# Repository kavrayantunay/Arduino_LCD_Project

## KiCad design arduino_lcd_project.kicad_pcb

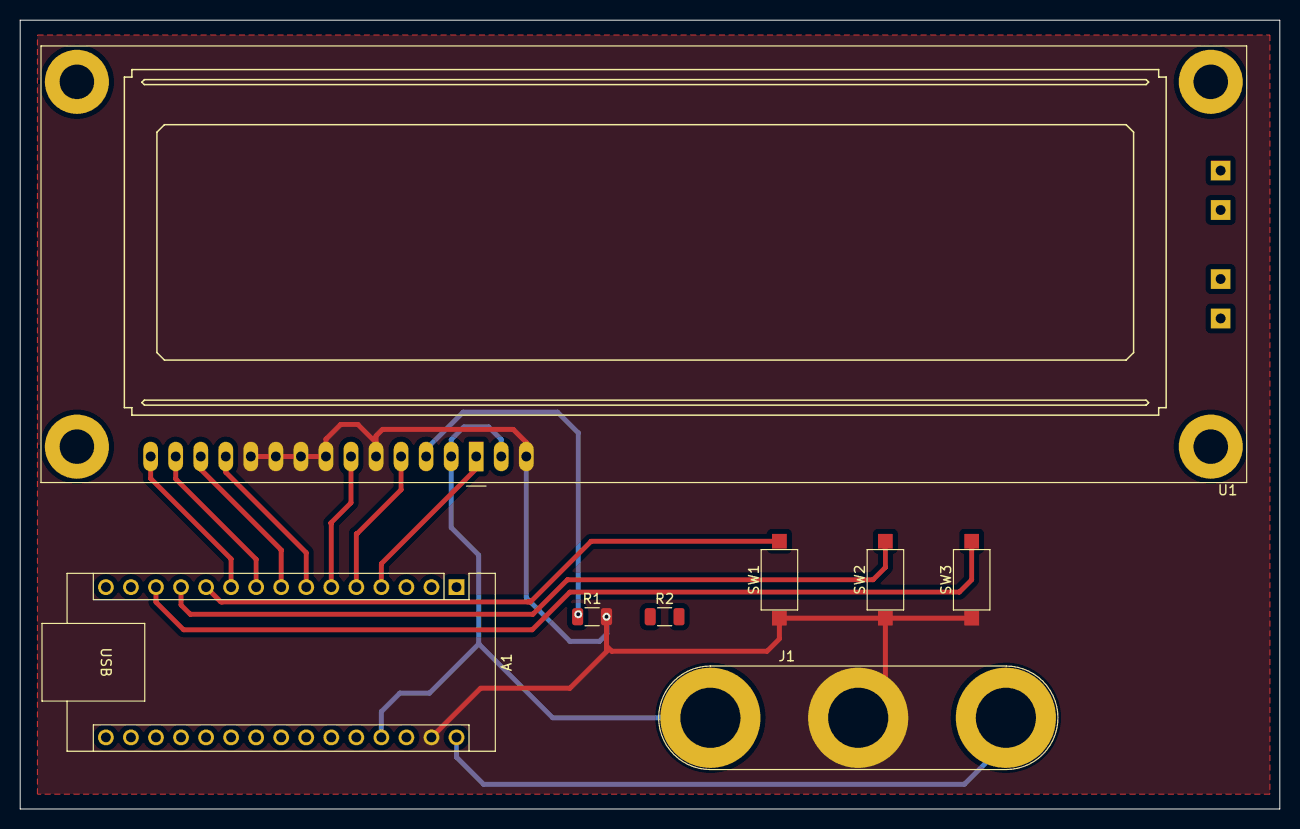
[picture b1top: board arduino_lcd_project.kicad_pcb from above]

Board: 2 copper layers, 127.8 x 80.0 mm, 8 parts (0 on the bottom side), 14 nets.

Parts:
A1: Arduino_Nano_v2.x; Arduino_Nano
J1: Conn_01x03_Female; Banana_Jack_3Pin
R1, R2: R; R_1206_3216Metric
SW1, SW2, SW3: SW_Push; SW_SPST_CK_RS282G05A3
U1: LCD-016N002L

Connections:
GND: A1.29 (GND), J1.2, R1.2, SW1.1, SW2.1, SW3.1, U1.5 (R/~W), U1.7 (DB0), U1.8 (DB1), U1.9 (DB2), U1.10 (DB3), U1.16 (K)
unnamed: A1.4 (GND), U1.1 (VSS)
unnamed: A1.5 (D2), U1.4 (RS)
unnamed: A1.6 (D3), U1.6 (E)
unnamed: A1.7 (D4), U1.11 (DB4)
unnamed: A1.8 (D5), U1.12 (DB5)
unnamed: A1.9 (D6), U1.13 (DB6)
unnamed: A1.10 (D7), U1.14 (DB7)
unnamed: A1.11 (D8), SW1.2
unnamed: A1.12 (D9), SW2.2
unnamed: A1.13 (D10), SW3.2
unnamed: A1.27 (+5V), J1.1, U1.2 (VDD), U1.15 (A/VEE)
unnamed: A1.30 (VIN), J1.3
unnamed: R1.1, U1.3 (VO)
